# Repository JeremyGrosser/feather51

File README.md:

# FEATHER51

**This project is a work in progress**

FEATHER51 is an [Adafruit Feather](https://learn.adafruit.com/adafruit-feather/feather-specification) compatible main-board using the Silicon Labs EFM8UB1 microcontroller. It is designed to be an easy entry point for learning assembly language on real hardware using an open source toolchain. This project is Open Source Hardware! See [LICENSE](LICENSE) for details.

**Arduino for people that want to learn Assembly**

# Project status

Ten revision A boards have been manufactured and tested with no known defects. The efm8flash utility is being developed as a portable open source flash programming tool for the factory USB bootloader. It has bugs.

A small number of JLink to C2D adapter boards are available for debugging using
the six pin header, though this adapter shouldn't be needed for most
applications.

[Schematic](feather51/feather51.pdf)

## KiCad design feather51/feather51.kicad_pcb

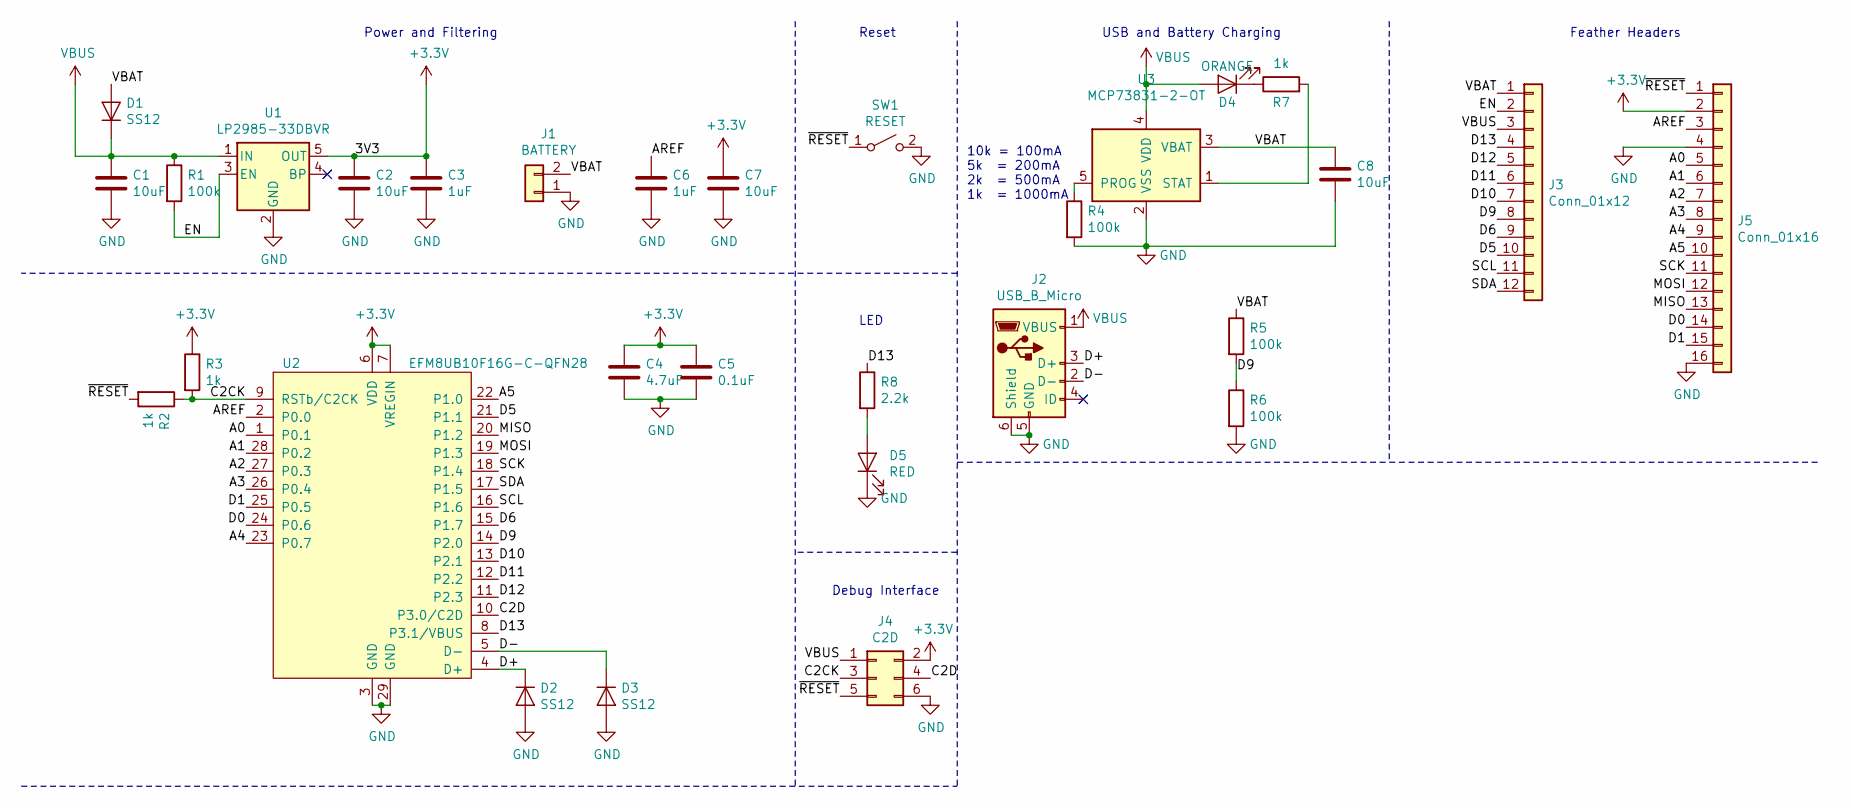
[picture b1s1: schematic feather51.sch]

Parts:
C1, C2, C7, C8: 10uF; C_0805_2012Metric
C3, C6: 1uF; C_0805_2012Metric
C4: 4.7uF; C_0805_2012Metric
C5: 0.1uF; C_0805_2012Metric
D1, D2, D3: SS12; DO-214AC
D4: ORANGE; LED_0603_1608Metric
D5: RED; LED_0603_1608Metric
J1: BATTERY; JST_PH_S2B-PH-K_1x02_P2.00mm_Horizontal
J2: USB_B_Micro; USB_Micro-B_Amphenol_10103594-0001LF_Horizontal
J3: Conn_01x12; PinSocket_1x12_P2.54mm_Vertical
J4: C2D; PinHeader_2x03_P2.54mm_Vertical
J5: Conn_01x16; PinSocket_1x16_P2.54mm_Vertical
R1, R4, R5, R6: 100k; R_0603_1608Metric
R2, R3, R7: 1k; R_0603_1608Metric
R8: 2.2k; R_0603_1608Metric
SW1: RESET; SW_SPST_B3U-1000P
U1: LP2985-33DBVR; SOT-23-5
U2: EFM8UB10F16G-C-QFN28; QFN-28-1EP_5x5mm_P0.5mm_EP3.35x3.35mm
U3: MCP73831-2-OT; SOT-23-5

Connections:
+3V3: C2.1, C3.1, C4.1, C5.1, C7.1, J4.2, J5.2, R3.1, U1.5 (OUT), U2.6 (VDD), U2.7 (VREGIN)
/A0: J5.5, U2.1 (P0.1)
/A1: J5.6, U2.28 (P0.2)
/A2: J5.7, U2.27 (P0.3)
/A3: J5.8, U2.26 (P0.4)
/A4: J5.9, U2.23 (P0.7)
/A5: J5.10, U2.22 (P1.0)
/AREF: C6.1, J5.3, U2.2 (P0.0)
/C2CK: J4.3, R2.1, R3.2, U2.9 (RSTb/C2CK)
/C2D: J4.4, U2.10 (P3.0/C2D)
/D0: J5.14, U2.24 (P0.6)
/D1: J5.15, U2.25 (P0.5)
/D5: J3.10, U2.21 (P1.1)
/D6: J3.9, U2.15 (P1.7)
/D9: J3.8, R5.2, R6.1, U2.14 (P2.0)
/D10: J3.7, U2.13 (P2.1)
/D11: J3.6, U2.12 (P2.2)
/D12: J3.5, U2.11 (P2.3)
/D13: J3.4, R8.1, U2.8 (P3.1/VBUS)
/D+: D2.1 (K), J2.3 (D+), U2.4 (D+)
/D-: D3.1 (K), J2.2 (D-), U2.5 (D-)
/EN: J3.2, R1.2, U1.3 (EN)
/MISO: J5.13, U2.20 (P1.2)
/MOSI: J5.12, U2.19 (P1.3)
/SCK: J5.11, U2.18 (P1.4)
/SCL: J3.11, U2.16 (P1.6)
/SDA: J3.12, U2.17 (P1.5)
/VBAT: C8.2, D1.2 (A), J1.2, J3.1, R5.1, U3.3 (VBAT)
/~RESET: J4.5, J5.1, R2.2, SW1.1 (A)
GND: C1.2, C2.2, C3.2, C4.2, C5.2, C6.2, C7.2, C8.1, D2.2 (A), D3.2 (A), D5.1 (K), J1.1, J2.5 (GND), J2.6 (Shield), J4.6, J5.4, J5.16, R4.2, R6.2, SW1.2 (B), U1.2 (GND), U2.3 (GND), U2.29 (GND), U3.2 (VSS)
unnamed: D4.1 (K), R7.1
unnamed: D5.2 (A), R8.2
unnamed: R4.1, U3.5 (PROG)
unnamed: R7.2, U3.1 (STAT)
VBUS: C1.1, D1.1 (K), D4.2 (A), J2.1 (VBUS), J3.3, J4.1, R1.1, U1.1 (IN), U3.4 (VDD)

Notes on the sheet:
Feather Headers
Power and Filtering
Reset
10k = 100mA 5k = 200mA 2k = 500mA 1k = 1000mA
USB and Battery Charging
LED
Debug Interface

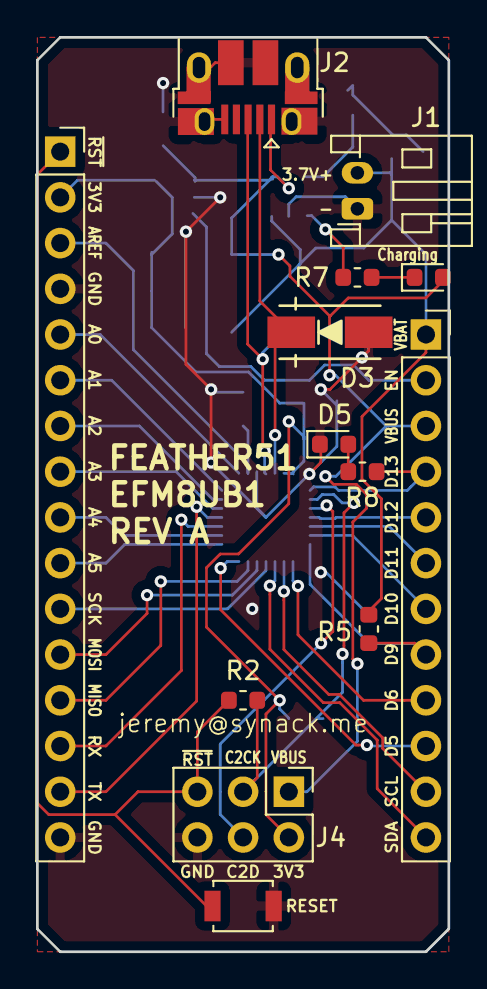
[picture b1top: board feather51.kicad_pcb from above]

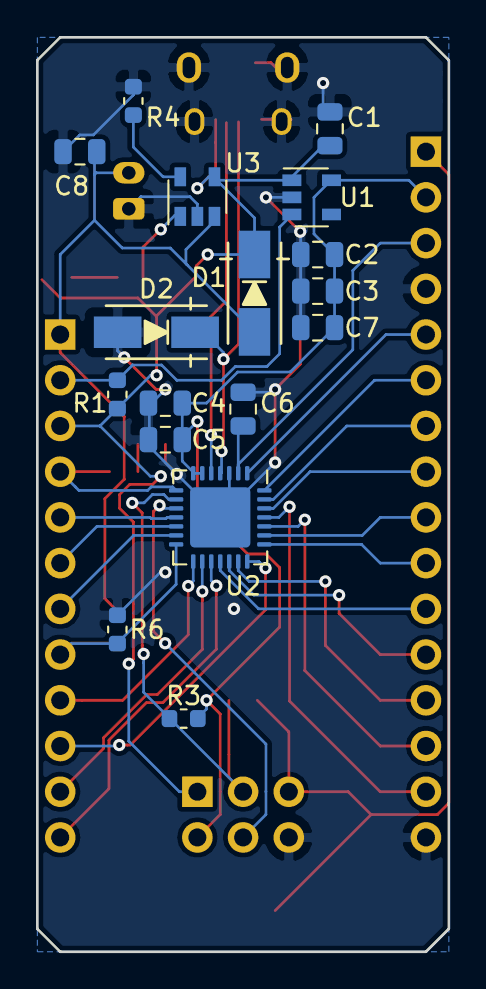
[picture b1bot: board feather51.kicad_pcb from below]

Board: 2 copper layers, 22.9 x 50.8 mm, 30 parts (17 on the bottom side), 35 nets.

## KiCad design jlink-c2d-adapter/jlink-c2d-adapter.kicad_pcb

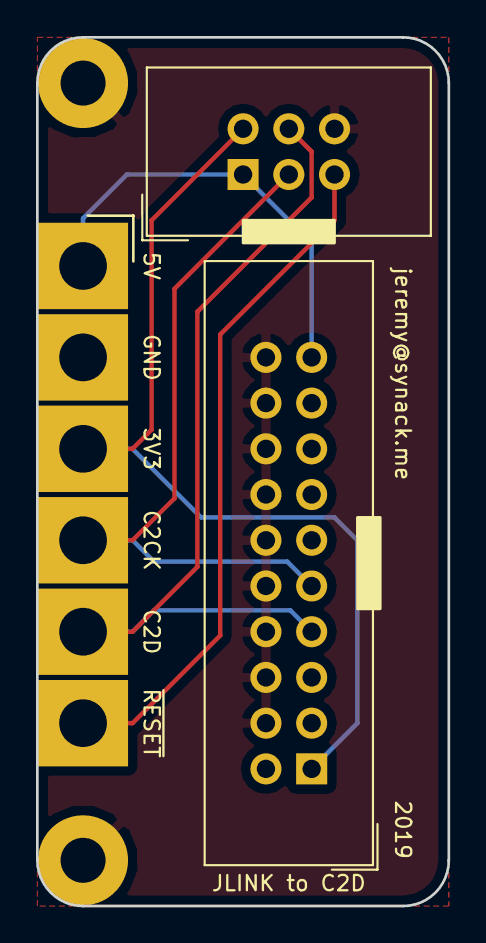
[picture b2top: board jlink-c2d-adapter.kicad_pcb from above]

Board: 2 copper layers, 22.9 x 48.3 mm, 3 parts (0 on the bottom side), 6 nets.

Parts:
J1: JLINK; IDC-Header_2x10_P2.54mm_Vertical
J2: C2D; IDC-Header_2x03_P2.54mm_Vertical
J4: EdgeClip; CardEdge6P

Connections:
+3V3: J1.1, J2.2, J4.3
+5V: J1.19, J2.1, J4.1
/TCK_C2CK: J1.9, J2.3, J4.4
/TMS_C2D: J1.7, J2.4, J4.5
/~RESET: J2.5, J4.6
GND: J1.4, J1.6, J1.8, J1.10, J1.12, J1.14, J1.16, J1.18, J1.20, J2.6, J4.2

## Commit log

2019-04-15 0.7mil spacing is wrong
2019-04-16 Layout locked
2019-04-16 Released to Manufacturing
2019-04-16 Blinky and docs
2019-04-16 Add revision A schematic PDF
2019-04-16 now in color!
2019-04-17 Add LICENSE, README, fix PDF rotation
2019-04-17 Link to schematic from README
2019-04-17 Add board renders
2019-04-17 whitespace, remove commented code
2019-04-17 Note about mounting hole clearance
2019-04-17 Disable internal voltage regulator
2019-04-18 Test fixture specification
2019-04-30 Split device-specific init out, fancier makefile.
2019-04-30 More makefile shenanigans
2019-05-02 skeleton for efm8flash
2019-05-03 Working single byte flash
2019-05-03 remove unused define
2019-05-04 autoreconf
2019-05-08 blinky: Generate a binary output file
2019-05-08 efm8flash: Read binary from file, write to flash in 8 byte blocks.
2019-05-08 Add README and LICENSE for efm8flash
2019-05-09 Update project status in README
2019-05-17 Split crc16 into a header, add unit tests
2019-05-17 commit test-driver
2019-05-17 efm8flash successfully flashes a program! verification currently disabled
2019-05-17 Add JLink to C2D adapter board, handy for debugging.
2019-05-17 A note about the jlink-c2d-adapter board in README
2019-05-24 Update diode and LDO part numbers to match as-built revision A boards
2019-05-28 monolithic blinky, add bootloader docs
2019-05-28 Blink faster!
2019-06-01 Motor blink
2019-06-08 Add Intel app notes for MCS-51

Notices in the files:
feather51/feather51.sch:
Creative Commons Attribution-ShareAlike 4.0 International License
